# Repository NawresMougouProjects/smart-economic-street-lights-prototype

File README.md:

# smart-economic-street-lights-prototype
## this is the PCB design:

## this is the schematic:

## this is the final result:

https://user-images.githubusercontent.com/62567205/175432200-66ff4771-56ad-432a-878b-4be2126c29c2.mp4

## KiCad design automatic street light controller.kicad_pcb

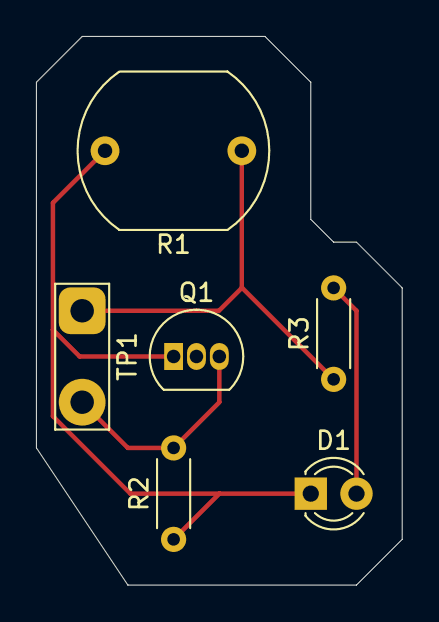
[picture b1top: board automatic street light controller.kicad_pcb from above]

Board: 2 copper layers, 20.3 x 30.5 mm, 6 parts (0 on the bottom side), 4 nets.

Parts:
D1: LED; LED_D3.0mm
Q1: BC547; TO-92_Inline
R1: LDR03; R_LDR_10x8.5mm_P7.6mm_Vertical
R2: R; R_Axial_DIN0204_L3.6mm_D1.6mm_P5.08mm_Horizontal
R3: 470; R_Axial_DIN0204_L3.6mm_D1.6mm_P5.08mm_Horizontal
TP1: TestPoint_2Pole; TestPoint_2Pads_Pitch5.08mm_Drill1.3mm

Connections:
unnamed: D1.1, Q1.1, R1.2, R2.1
unnamed: D1.2, R3.2
unnamed: Q1.3, R2.2, TP1.2
unnamed: R1.1, R3.1, TP1.1
